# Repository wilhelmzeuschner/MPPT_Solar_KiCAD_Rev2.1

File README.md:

# Maximum Power Point Tracker for Solar Panels

This project was done as part of my studies at university. It's intended use case is for my [University's solar boat team](https://www.hs-emden-leer.de/studierende/fachbereiche/technik/projekte/solarboot).

## Technical Overview:

- 150W input power
- Boost Converter: Uin < Uout
- STM32 Microcontroller
- CAN Communications (software support lacking as of April 2022)

## How to use this repo:

### Schematic:
The schematic can be found here: https://github.com/wilhelmzeuschner/MPPT_Solar_KiCAD_Rev2.1/blob/main/pcb/export/Schematic.pdf

### Code:
The source code is located here: https://github.com/wilhelmzeuschner/MPPT_Solar_KiCAD_Rev2.1/tree/main/code/MPPT_Main

Platform IO was used for programming, just clone the repo and open the folder / workspace. The Arduino framework was used for the firmware.

### PCB:
The PCB was designed with KiCAD V6, the files are located here: https://github.com/wilhelmzeuschner/MPPT_Solar_KiCAD_Rev2.1/tree/main/pcb/kicad_files

### Bill of Materials (BOM):
The BOM file is also provided, although some parts are not available as of April 2022 due to the semiconductor shortage.
https://github.com/wilhelmzeuschner/MPPT_Solar_KiCAD_Rev2.1/tree/main/bom

### CAD Files for a 3D-printable Case:
https://github.com/wilhelmzeuschner/MPPT_Solar_KiCAD_Rev2.1/tree/main/cad

## Further documentation:

This project was documented extensively. The technical report can be found here:
https://github.com/wilhelmzeuschner/MPPT_Solar_KiCAD_Rev2.1/blob/main/doc/latex/pdf/Projektarbeit_MPPT_Wilhelm_Zeuschner_GitHub.pdf

### License:

MIT License

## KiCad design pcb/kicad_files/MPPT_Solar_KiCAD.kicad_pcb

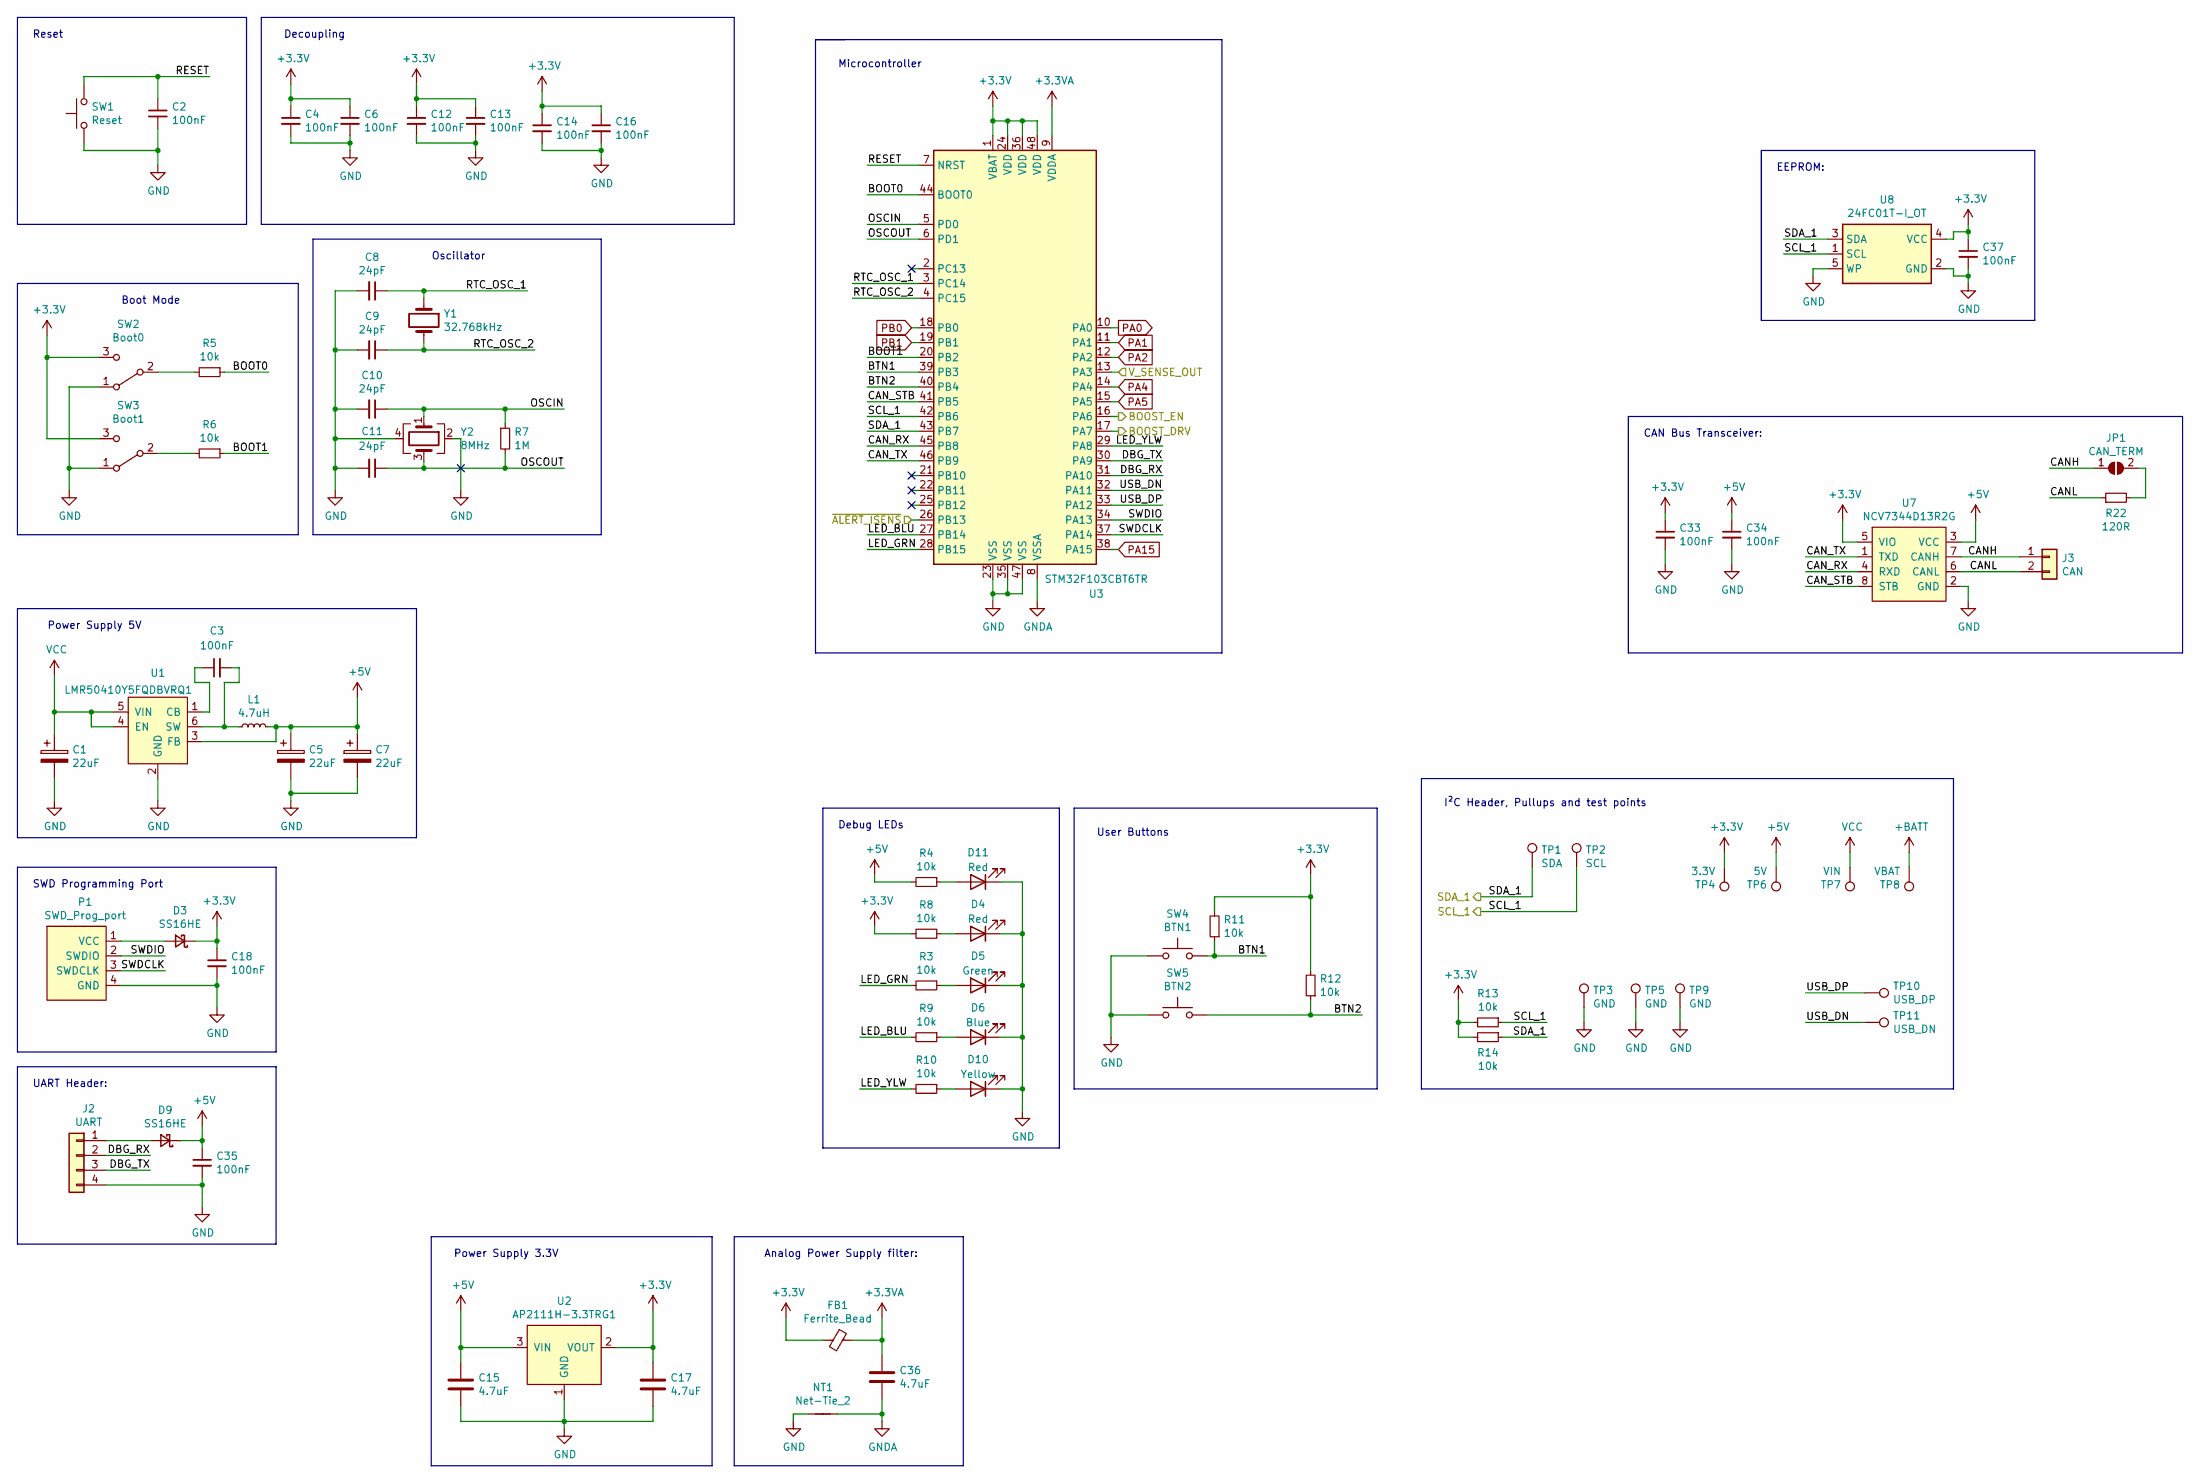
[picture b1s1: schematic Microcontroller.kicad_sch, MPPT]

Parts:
C1, C5, C7: 22uF; CP_Elec_5x5.9; Manufacturer Part Number 865080643008; Digikey Part No PCE5022CT-ND
C2, C3, C4, C6, C12, C13, C14, C16, C18, C33, C34, C35, C37: 100nF; C_0603_1608Metric; Manufacturer Part Number LMK063C6104KP-F; Digikey Part No 1276-CL10B104KB8NNNLCT-ND
C8, C9, C10, C11: 24pF; C_0603_1608Metric; Manufacturer Part Number 80-C0603C240G1HACTU; Digikey Part No 1276-1761-1-ND
C15, C17, C36: 4.7uF; C_0805_2012Metric; Manufacturer Part Number 885012107013; Digikey Part No 1276-1244-1-ND
D3, D9: SS16HE; D_SOD-323; Manufacturer Part Number SS16HE; Digikey Part No SS16HECT-ND
D4, D11: Red; LED_0805_2012Metric; Manufacturer Part Number 150080RS75000; Digikey Part No 732-4984-1-ND
D5: Green; LED_0805_2012Metric; Manufacturer Part Number 150080GS75000; Digikey Part No 732-4983-1-ND
D6: Blue; LED_0805_2012Metric; Manufacturer Part Number 150080BS75000; Digikey Part No 732-4982-1-ND
D10: Yellow; LED_0805_2012Metric; Manufacturer Part Number 150080YS75000; Digikey Part No 732-4987-1-ND
FB1: Ferrite_Bead; L_0603_1608Metric; Manufacturer Part Number BLM18TG102TN1D; Digikey Part No 490-9701-1-ND
J2: UART; PinHeader_1x04_P2.54mm_Vertical; Manufacturer Part Number RS1-04-G; Digikey Part No 2057-RS1-04-G-ND
J3: CAN; 1713017; Manufacturer Part Number 1713017; Digikey Part No 277-8591-ND
JP1: CAN_TERM; SolderJumper-2_P1.3mm_Open_RoundedPad1.0x1.5mm
L1: 4.7uH; 60x60mm_Inductor; Manufacturer Part Number NRS6028T4R7MMGK; Digikey Part No 587-2943-1-ND
NT1: Net-Tie_2; NetTie-2_SMD_Pad0.5mm
P1: SWD_Prog_port; PinSocket_1x04_P2.54mm_Vertical; Manufacturer Part Number RS1-04-G; Digikey Part No 2057-RS1-04-G-ND
R3, R4, R5, R6, R8, R9, R10, R11, R12, R13, R14: 10k; R_0603_1608Metric; Manufacturer Part Number RC0603FR-0710KL; Digikey Part No 311-10.0KHRCT-ND
R7: 1M; R_0603_1608Metric; Manufacturer Part Number RC0603FR-071ML; Digikey Part No 311-1.00MHRCT-ND
R22: 120R; R_1206_3216Metric; Manufacturer Part Number RC1206FR-07120RL; Digikey Part No 311-120FRCT-ND
SW1: Reset; SW_SPST_EVQPE1; Manufacturer Part Number CKN12317-1-ND; Digikey Part No CKN12317-1-ND
SW2: Boot0; SW_JS202011JCQN; Manufacturer Part Number JS202011JCQN; Digikey Part No CKN10723CT-ND
SW3: Boot1; SW_JS202011JCQN; Manufacturer Part Number JS202011JCQN; Digikey Part No CKN10723CT-ND
SW4: BTN1; SW_SPST_EVQPE1; Manufacturer Part Number CKN12317-1-ND; Digikey Part No CKN12317-1-ND
SW5: BTN2; SW_SPST_EVQPE1; Manufacturer Part Number CKN12317-1-ND; Digikey Part No CKN12317-1-ND
TP1: SDA; TestPoint_Pad_D1.0mm
TP2: SCL; TestPoint_Pad_D1.0mm
TP3, TP5, TP9: GND; TestPoint_Pad_D1.0mm
TP4: 3.3V; TestPoint_Pad_D1.0mm
TP6: 5V; TestPoint_Pad_D1.0mm
TP7: VIN; TestPoint_Pad_D1.0mm
TP8: VBAT; TestPoint_Pad_D1.0mm
TP10: USB_DP; TestPoint_Pad_D1.0mm
TP11: USB_DN; TestPoint_Pad_D1.0mm
U1: LMR50410Y5FQDBVRQ1; SOT-23-6; Manufacturer Part Number LMR50410Y5FQDBVRQ1; Digikey Part No 296-LMR50410Y5FQDBVRQ1CT-ND
U2: AP2111H-3.3TRG1; SOT-223-3_TabPin2; Manufacturer Part Number AP2111H-3.3TRG1; Digikey Part No AP2111H-3.3TRG1DICT-ND
U3: STM32F103CBT6TR; LQFP-48_7x7mm_P0.5mm; Manufacturer Part Number STM32F103CBT6TR; Digikey Part No 497-17380-1-ND
U7: NCV7344D13R2G; SOIC-8_3.9x4.9mm_P1.27mm; Manufacturer Part Number NCV7344D13R2G; Digikey Part No NCV7344D13R2GOSCT-ND
U8: 24FC01T-I_OT; SOT-23-5; Manufacturer Part Number 24FC01T-I/OT; Digikey Part No 24FC01T-I/OTCT-ND
Y1: 32.768kHz; Crystal_SMD_MicroCrystal_CC7V-T1A-2Pin_3.2x1.5mm; Manufacturer Part Number FC-135R 32.7680KF-A3; Digikey Part No SER4076CT-ND
Y2: 8MHz; Crystal_SMD_3225-4Pin_3.2x2.5mm; Manufacturer Part Number ECS-80-12-33Q-GN-TR; Digikey Part No 50-ECS-80-12-33Q-GN-CT-ND

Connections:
+3.3VA: C36.1, FB1.1, U3.9 (VDDA); also elsewhere on the board
+3V3: C4.1, C6.1, C12.1, C13.1, C14.1, C16.1, C17.1, C18.1, C33.1, C37.1, D3.1 (K), FB1.2, R8.2, R11.2, R12.2, R13.2, R14.2, SW2.3 (C), SW3.3 (C), TP4.1, U2.2 (VOUT), U2.4 (VOUT), U3.1 (VBAT), U3.24 (VDD), U3.36 (VDD), U3.48 (VDD), U7.5 (VIO), U8.4 (VCC); also elsewhere on the board
+5V: C5.1, C7.1, C15.1, C34.1, C35.1, D9.1 (K), L1.2, R4.2, TP6.1, U1.3 (FB), U2.3 (VIN), U7.3 (VCC)
+BATT: TP8.1; also elsewhere on the board
/MPPT_Boost_Converter/BOOST_DRV: U3.17 (PA7); also elsewhere on the board
/MPPT_Boost_Converter/BOOST_EN: U3.16 (PA6); also elsewhere on the board
/MPPT_Boost_Converter/V_SENSE_OUT: U3.13 (PA3); also elsewhere on the board
/MPPT_Boost_Converter/~ALERT_ISENS: U3.26 (PB13); also elsewhere on the board
/Microcontroller/BOOT0: R5.1, U3.44 (BOOT0)
/Microcontroller/BOOT1: R6.1, U3.20 (PB2)
/Microcontroller/BTN1: R11.1, SW4.2, U3.39 (PB3)
/Microcontroller/BTN2: R12.1, SW5.2, U3.40 (PB4)
/Microcontroller/CANH: J3.1, JP1.1 (A), U7.7 (CANH)
/Microcontroller/CANL: J3.2, R22.1, U7.6 (CANL)
/Microcontroller/CAN_RX: U3.45 (PB8), U7.4 (RXD)
/Microcontroller/CAN_STB: U3.41 (PB5), U7.8 (STB)
/Microcontroller/CAN_TX: U3.46 (PB9), U7.1 (TXD)
/Microcontroller/DBG_RX: J2.2, U3.31 (PA10)
/Microcontroller/DBG_TX: J2.3, U3.30 (PA9)
/Microcontroller/LED_BLU: R9.2, U3.27 (PB14)
/Microcontroller/LED_GRN: R3.2, U3.28 (PB15)
/Microcontroller/LED_YLW: R10.2, U3.29 (PA8)
/Microcontroller/OSCIN: C10.1, R7.1, U3.5 (PD0), Y2.1
/Microcontroller/OSCOUT: C11.1, R7.2, U3.6 (PD1), Y2.3
/Microcontroller/RESET: C2.1, SW1.2, U3.7 (NRST)
/Microcontroller/RTC_OSC_1: C8.1, U3.3 (PC14), Y1.1
/Microcontroller/RTC_OSC_2: C9.1, U3.4 (PC15), Y1.2
/Microcontroller/SCL_1: R13.1, TP2.1, U3.42 (PB6), U8.1 (SCL); also elsewhere on the board
/Microcontroller/SDA_1: R14.1, TP1.1, U3.43 (PB7), U8.3 (SDA); also elsewhere on the board
/Microcontroller/SWDCLK: P1.3 (SWDCLK), U3.37 (PA14)
/Microcontroller/SWDIO: P1.2 (SWDIO), U3.34 (PA13)
/Microcontroller/USB_DN: TP11.1, U3.32 (PA11)
/Microcontroller/USB_DP: TP10.1, U3.33 (PA12)
GND: C1.2, C2.2, C4.2, C5.2, C6.2, C7.2, C8.2, C9.2, C10.2, C11.2, C12.2, C13.2, C14.2, C15.2, C16.2, C17.2, C18.2, C33.2, C34.2, C35.2, C37.2, D4.1 (K), D5.1 (K), D6.1 (K), D10.1 (K), D11.1 (K), J2.4, NT1.1, P1.4 (GND), SW1.1, SW2.1 (A), SW3.1 (A), SW4.1, SW5.1, TP3.1, TP5.1, TP9.1, U1.2 (GND), U2.1 (GND), U3.23 (VSS), U3.35 (VSS), U3.47 (VSS), U7.2 (GND), U8.2 (GND), U8.5 (WP), Y2.2, Y2.4; also elsewhere on the board
GNDA: C36.2, NT1.2, U3.8 (VSSA); also elsewhere on the board
unnamed: C3.1, U1.1 (CB)
unnamed: C3.2, L1.1, U1.6 (SW)
unnamed: D3.2 (A), P1.1 (VCC)
unnamed: D4.2 (A), R8.1
unnamed: D5.2 (A), R3.1
unnamed: D6.2 (A), R9.1
unnamed: D9.2 (A), J2.1
unnamed: D10.2 (A), R10.1
unnamed: D11.2 (A), R4.1
unnamed: JP1.2 (B), R22.2
unnamed: R5.2, SW2.2 (B)
unnamed: R6.2, SW3.2 (B)
PA0: U3.10 (PA0)
PA1: U3.11 (PA1)
PA2: U3.12 (PA2)
PA4: U3.14 (PA4)
PA5: U3.15 (PA5)
PA15: U3.38 (PA15)
PB0: U3.18 (PB0)
PB1: U3.19 (PB1)
VCC: C1.1, TP7.1, U1.4 (EN), U1.5 (VIN); also elsewhere on the board

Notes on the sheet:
CAN Bus Transceiver:
EEPROM:
Power Supply 3.3V
Reset
User Buttons
Analog Power Supply filter:
Microcontroller
SWD Programming Port
Power Supply 5V
Boot Mode
Decoupling
UART Header:
Debug LEDs
I²C Header, Pullups and test points
Oscillator

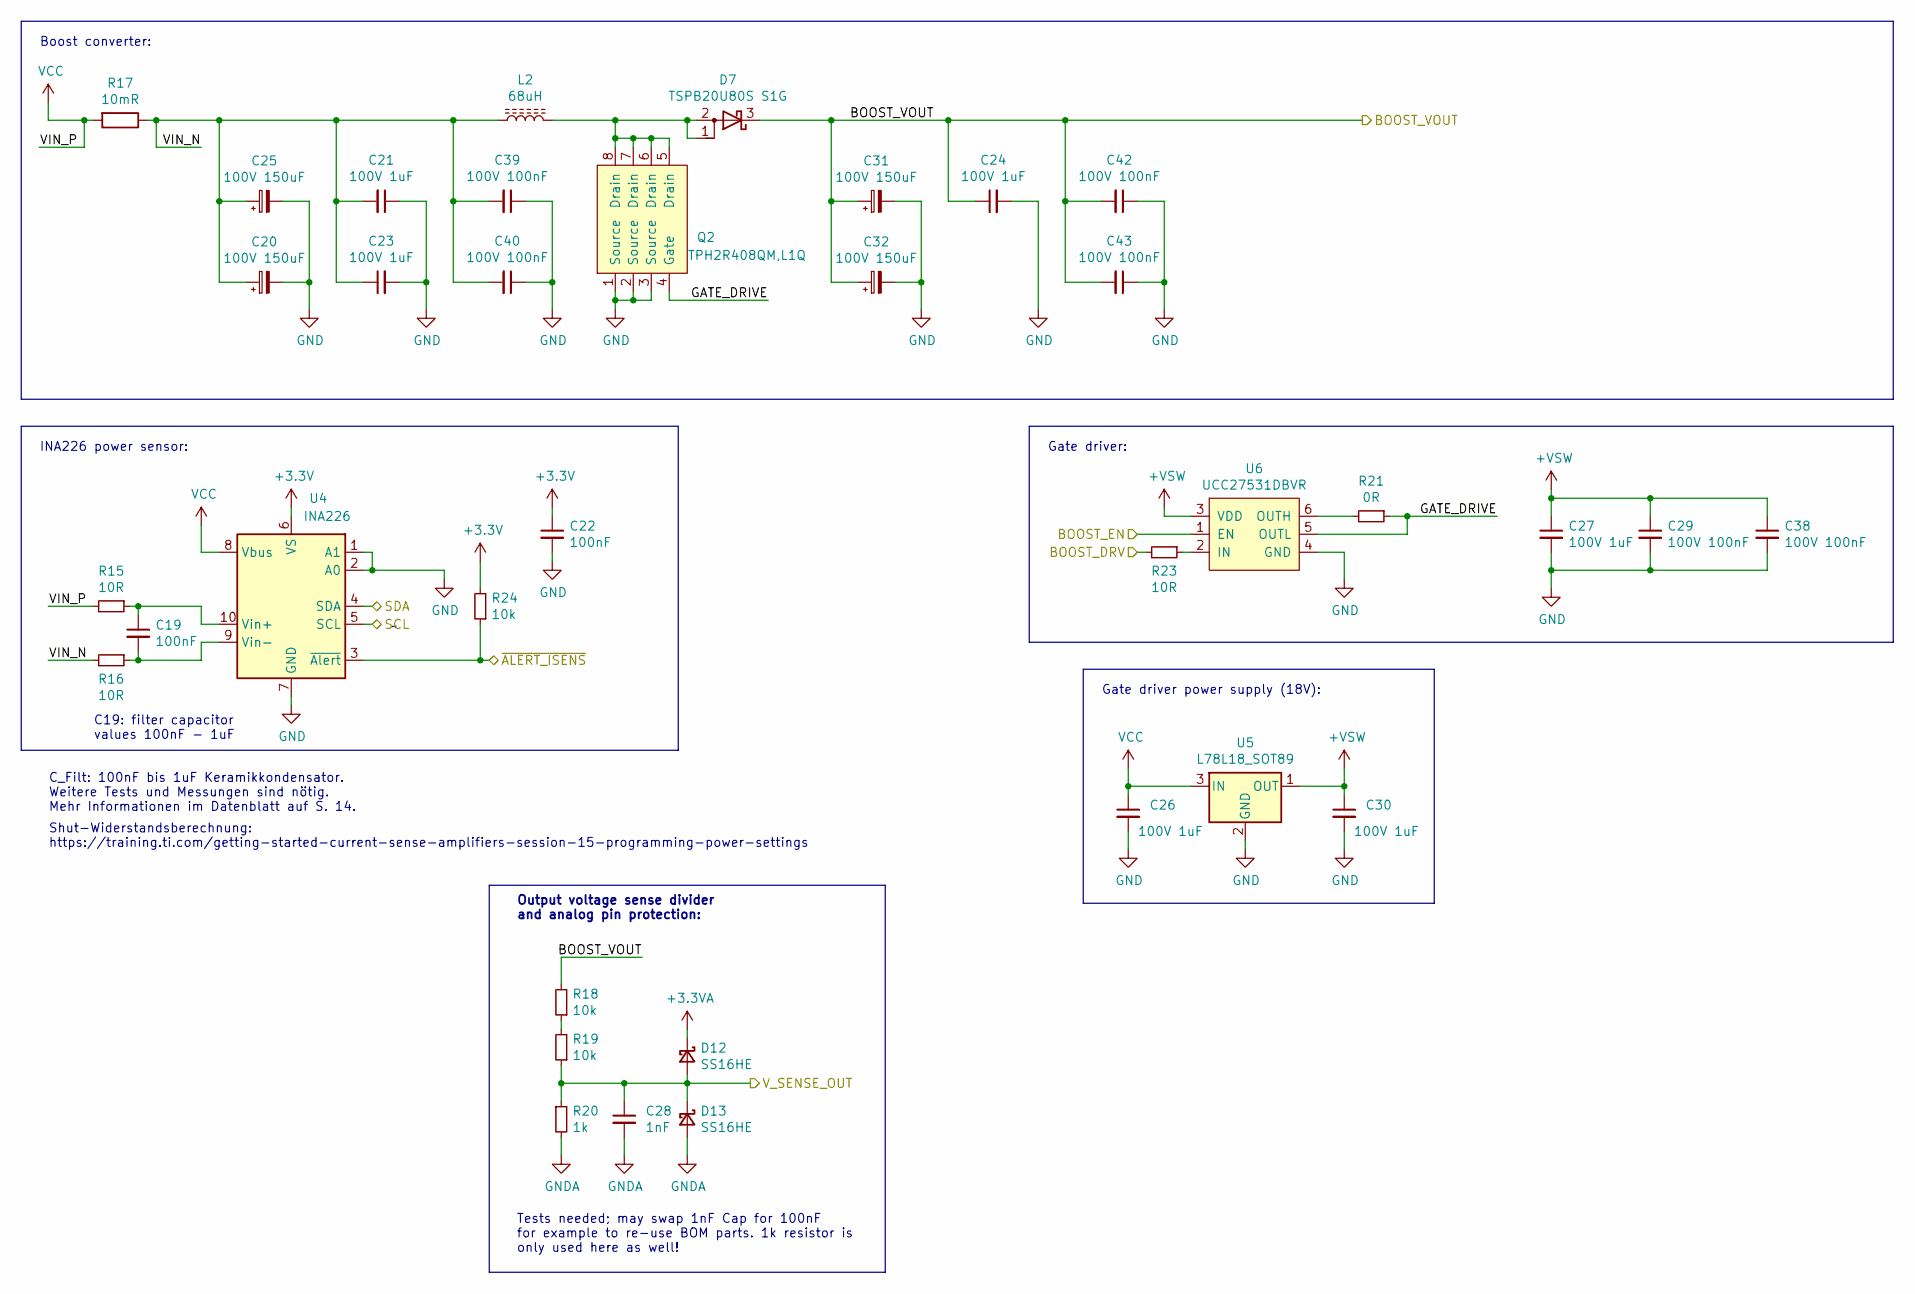
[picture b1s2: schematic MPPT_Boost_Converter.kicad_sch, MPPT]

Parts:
C19, C22: 100nF; C_0603_1608Metric; Manufacturer Part Number LMK063C6104KP-F; Digikey Part No 1276-CL10B104KB8NNNLCT-ND
C20, C25, C31, C32: 100V 150uF; CAPAE1300X1650N; Manufacturer Part Number EMHS101ARA151MKG5S; Digikey Part No 565-5086-1-ND
C21, C23, C24, C26, C27, C30: 100V 1uF; C_1206_3216Metric; Manufacturer Part Number HMK316BJ105KL-T; Digikey Part No 587-5021-1-ND
C28: 1nF; C_0603_1608Metric; Manufacturer Part Number C0603C102J5RACAUTO; Digikey Part No 399-12989-1-ND
C29, C38, C39, C40, C42, C43: 100V 100nF; C_0603_1608Metric; Manufacturer Part Number CL10B104KC8NNNC; Digikey Part No 587-6323-1-ND
D7: TSPB20U80S S1G; TO-277A; Manufacturer Part Number TSPB20U80S S1G; Digikey Part No TSPB20U80SS1GCT-ND
D12, D13: SS16HE; D_SOD-323; Manufacturer Part Number SS16HE; Digikey Part No SS16HECT-ND
L2: 68uH; 74437429203680; Manufacturer Part Number 74437429203680; Digikey Part No 732-11708-ND
Q2: TPH2R408QM,L1Q; SOP_ADVANCE; Manufacturer Part Number TPH2R408QM,L1Q; Digikey Part No 264-TPH2R408QML1QCT-ND
R15, R16, R23: 10R; R_0603_1608Metric; Manufacturer Part Number RMCF0603FT10R0; Digikey Part No RMCF0603FT10R0CT-ND
R17: 10mR; R_0612_1632Metric; Manufacturer Part Number CFG0612-FX-R010ELF; Digikey Part No CFG0612-FX-R010ELFCT-ND
R18, R19, R24: 10k; R_0603_1608Metric; Manufacturer Part Number RC0603FR-0710KL; Digikey Part No 311-10.0KHRCT-ND
R20: 1k; R_0603_1608Metric; Manufacturer Part Number CRCW06031K00FKEAC; Digikey Part No 541-3949-1-ND
R21: 0R; R_0603_1608Metric; Manufacturer Part Number RC0603FR-070RL; Digikey Part No 311-0.0HRCT-ND
U4: INA226; VSSOP-10_3x3mm_P0.5mm; Manufacturer Part Number INA226AIDGSR; Digikey Part No 296-29034-1-ND
U5: L78L18_SOT89; SOT-89-3; Manufacturer Part Number L78L18ACUTR; Digikey Part No 497-7280-1-ND
U6: UCC27531DBVR; SOT-23-6; Manufacturer Part Number UCC27531DBVR; Digikey Part No 296-35581-1-ND

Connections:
+3.3VA: D12.1 (K); also elsewhere on the board
+3V3: C22.1, R24.2, U4.6 (VS); also elsewhere on the board
+VSW: C27.1, C29.1, C30.1, C38.1, U5.1 (OUT), U6.3 (VDD)
/MPPT_Boost_Converter/BOOST_DRV: R23.2; also elsewhere on the board
/MPPT_Boost_Converter/BOOST_EN: U6.1 (EN); also elsewhere on the board
/MPPT_Boost_Converter/BOOST_VOUT: C24.1, C31.1, C32.1, C42.2, C43.2, D7.3 (K), R18.2; also elsewhere on the board
/MPPT_Boost_Converter/GATE_DRIVE: Q2.4 (Gate), R21.1, U6.5 (OUTL)
/MPPT_Boost_Converter/VIN_N: C20.1, C21.2, C23.1, C25.1, C39.2, C40.2, L2.1, R16.2, R17.1
/MPPT_Boost_Converter/V_SENSE_OUT: C28.1, D12.2 (A), D13.1 (K), R19.1, R20.1; also elsewhere on the board
/MPPT_Boost_Converter/~ALERT_ISENS: R24.1, U4.3 (~Alert); also elsewhere on the board
/Microcontroller/SCL_1: U4.5 (SCL); also elsewhere on the board
/Microcontroller/SDA_1: U4.4 (SDA); also elsewhere on the board
GND: C20.2, C21.1, C22.2, C23.2, C24.2, C25.2, C26.2, C27.2, C29.2, C30.2, C31.2, C32.2, C38.2, C39.1, C40.1, C42.1, C43.1, Q2.1 (Source), Q2.2 (Source), Q2.3 (Source), U4.1 (A1), U4.2 (A0), U4.7 (GND), U5.2 (GND), U6.4 (GND); also elsewhere on the board
GNDA: C28.2, D13.2 (A), R20.2; also elsewhere on the board
unnamed: C19.1, R15.1, U4.10 (Vin+)
unnamed: C19.2, R16.1, U4.9 (Vin-)
unnamed: D7.1 (A), D7.2 (A), L2.2, Q2.5 (Drain), Q2.6 (Drain), Q2.7 (Drain), Q2.8 (Drain)
unnamed: R18.1, R19.2
unnamed: R21.2, U6.6 (OUTH)
unnamed: R23.1, U6.2 (IN)
VCC: C26.1, R15.2, R17.2, U4.8 (Vbus), U5.3 (IN); also elsewhere on the board

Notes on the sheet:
Output voltage sense divider and analog pin protection:
C19: filter capacitor values 100nF - 1uF
Boost converter:
Shut-Widerstandsberechnung: https://training.ti.com/getting-started-current-sense-amplifiers-session-15-programming-power-settings
Gate driver:
Gate driver power supply (18V):
Tests needed; may swap 1nF Cap for 100nF for example to re-use BOM parts. 1k resistor is only used here as well!
INA226 power sensor:
C_Filt: 100nF bis 1uF Keramikkondensator. Weitere Tests und Messungen sind nötig. Mehr Informationen im Datenblatt auf S. 14.

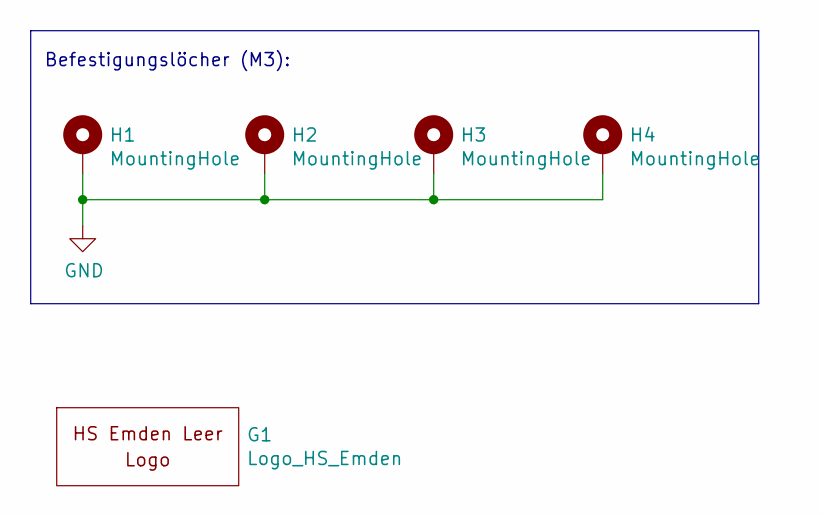
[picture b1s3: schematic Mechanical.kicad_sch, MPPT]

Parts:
G1: Logo_HS_Emden; HS_Logo
H1, H2, H3, H4: MountingHole; MountingHole_3.2mm_M3_Pad_Via

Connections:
GND: H1.1, H2.1, H3.1, H4.1; also elsewhere on the board

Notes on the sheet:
Befestigungslöcher (M3):

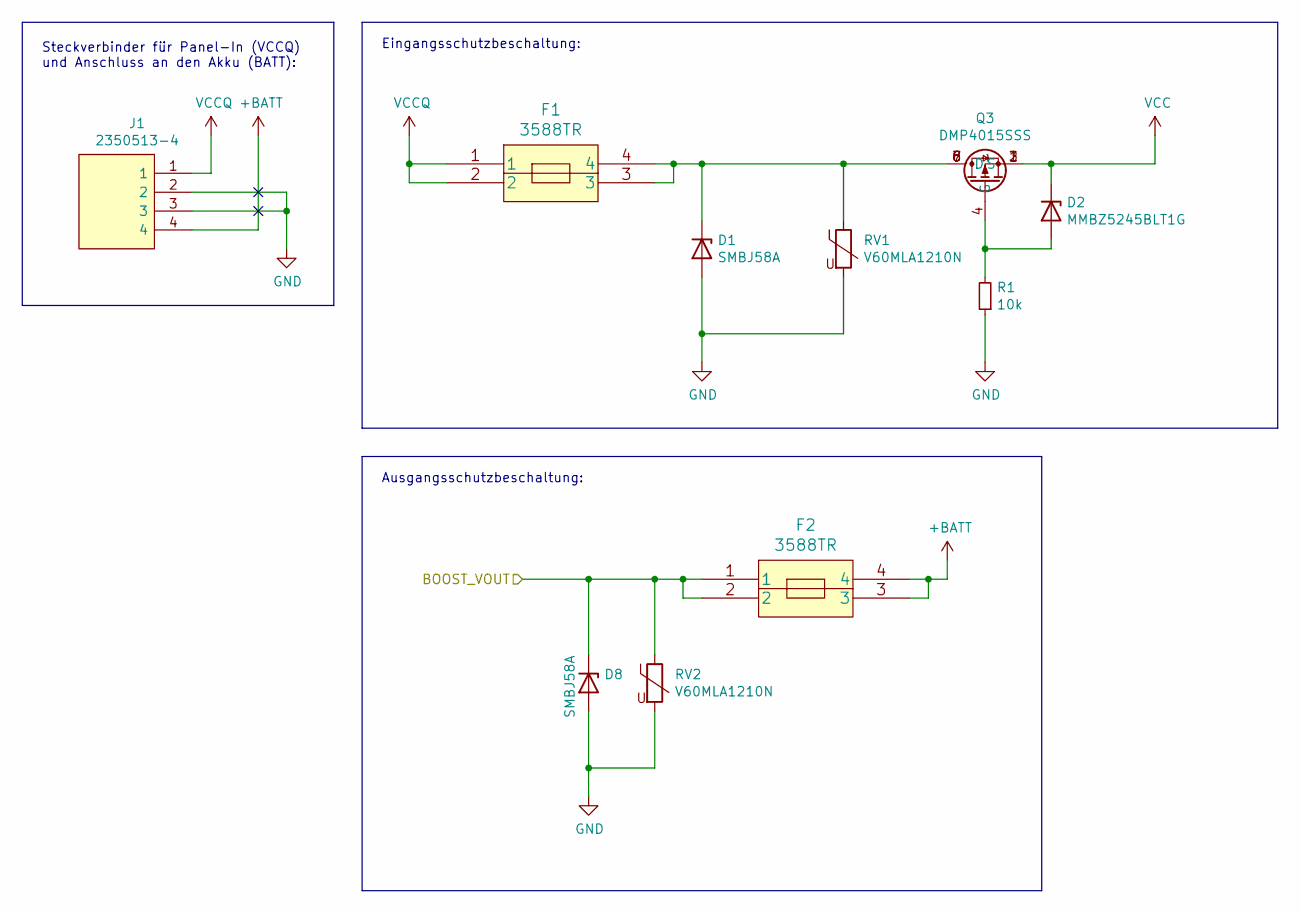
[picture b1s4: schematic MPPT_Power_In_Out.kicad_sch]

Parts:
D1, D8: SMBJ58A; D_SMB; Manufacturer Part Number SMBJ58A; Digikey Part No SMBJ58ALFCT-ND
D2: MMBZ5245BLT1G; D_SOT-23_ANK; Manufacturer Part Number MMBZ5245BLT1G; Digikey Part No MMBZ5245BLT1GOSCT-ND
F1, F2: 3588TR; Manufacturer Part Number 3588TR; Digikey Part No 36-3588CT-ND
J1: 2350513-4; SHDRRA4W110P0X500_1X4_2160X830X1230P; Manufacturer Part Number 2350513-4; Digikey Part No A145374-ND
Q3: DMP4015SSS; SO-8_3.9x4.9mm_P1.27mm; Manufacturer Part No DMP4015SSS-13; Digi-Key Part No DMP4015SSS-13DICT-ND
R1: 10k; R_0603_1608Metric; Manufacturer Part Number RC0603FR-0710KL; Digikey Part No 311-10.0KHRCT-ND
RV1, RV2: V60MLA1210N; R_1210_3225Metric; Manufacturer Part Number V60MLA1210NH; Digikey Part No F3830CT-ND

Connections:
+BATT: F2.3, F2.4, J1.4; also elsewhere on the board
/MPPT_Boost_Converter/BOOST_VOUT: D8.1 (K), F2.1, F2.2, RV2.1; also elsewhere on the board
GND: D1.2 (A), D8.2 (A), J1.2, J1.3, R1.1, RV1.2, RV2.2; also elsewhere on the board
unnamed: D1.1 (K), F1.3, F1.4, Q3.5 (D), Q3.6 (D), Q3.7 (D), Q3.8 (D), RV1.1
unnamed: D2.2 (A), Q3.4 (G), R1.2
VCC: D2.1 (K), Q3.1 (S), Q3.2 (S), Q3.3 (S); also elsewhere on the board
VCCQ: F1.1, F1.2, J1.1

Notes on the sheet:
Eingangsschutzbeschaltung:
Steckverbinder für Panel-In (VCCQ) und Anschluss an den Akku (BATT):
Ausgangsschutzbeschaltung:

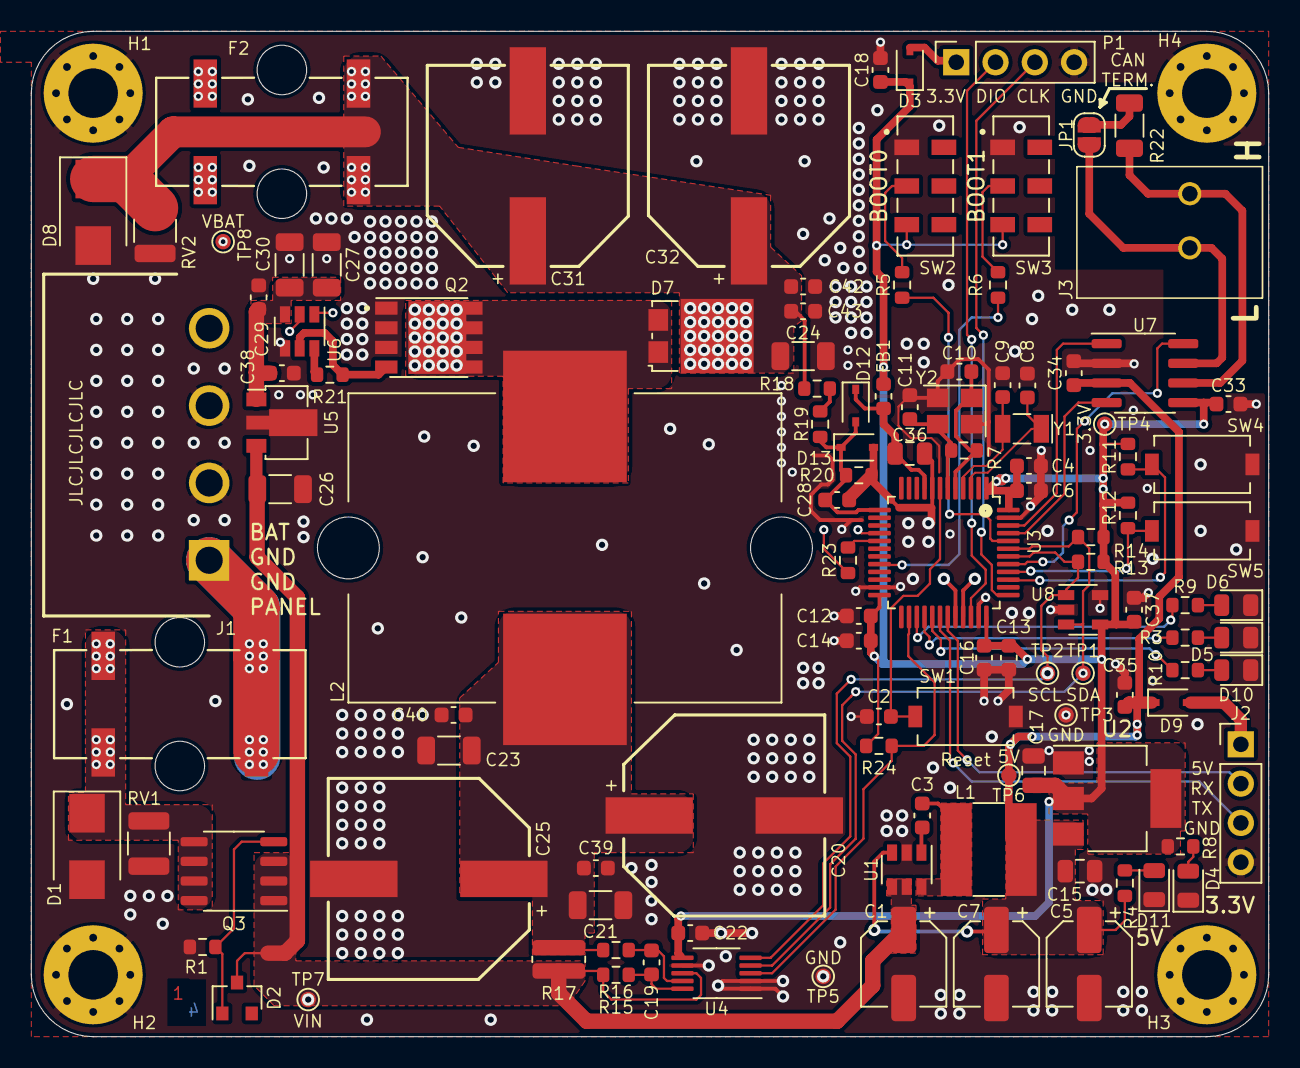
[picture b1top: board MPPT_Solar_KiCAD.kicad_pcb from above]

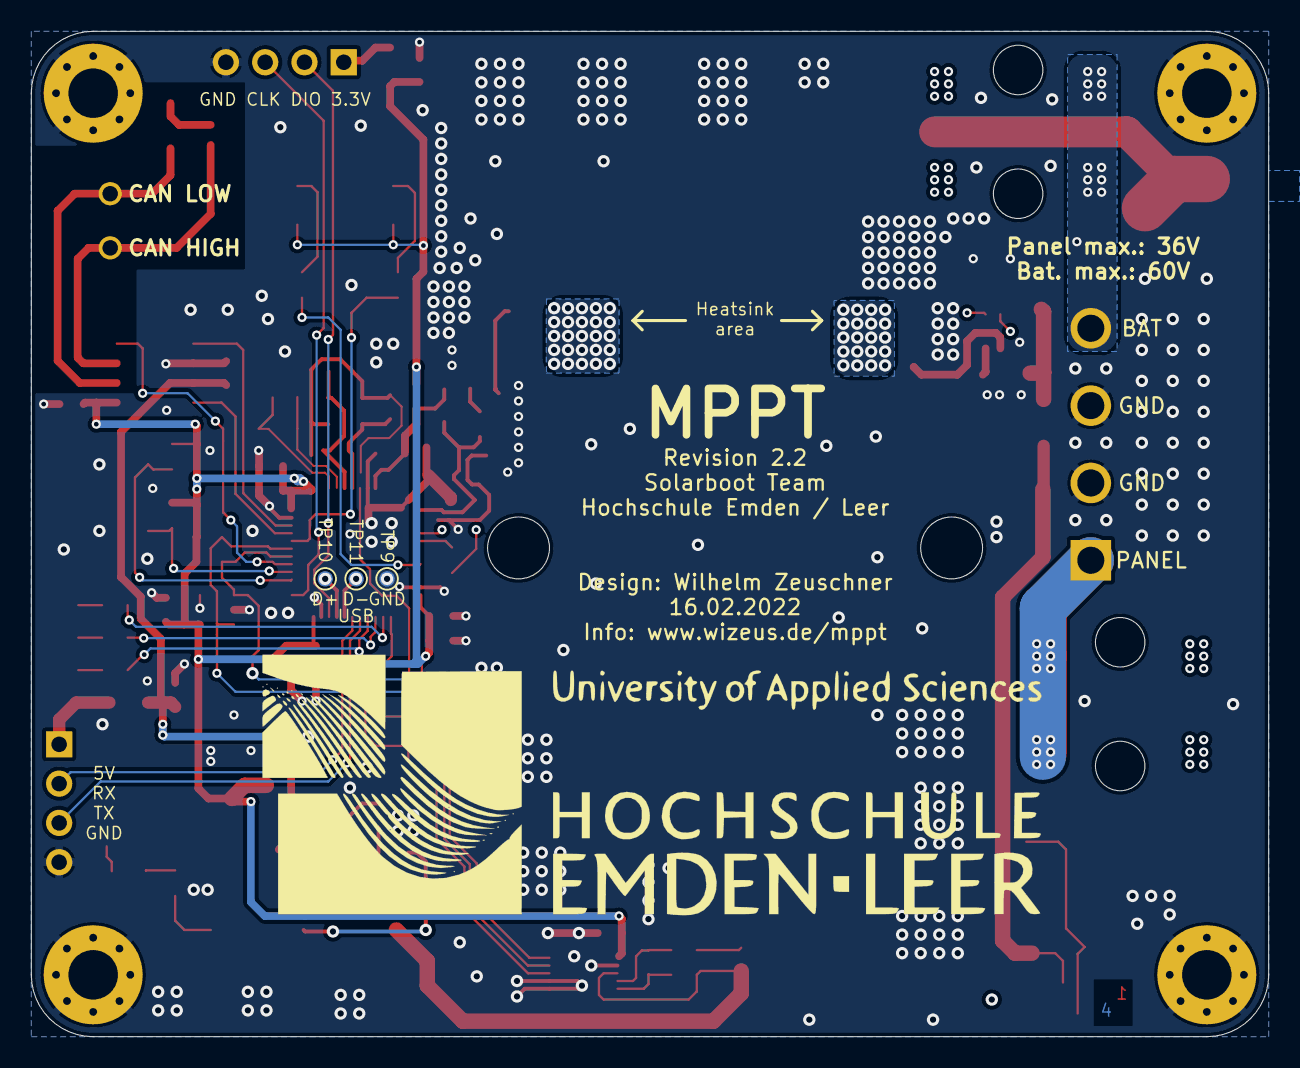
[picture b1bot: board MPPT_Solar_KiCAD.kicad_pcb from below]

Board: 4 copper layers, 80.0 x 65.0 mm, 124 parts (4 on the bottom side), 61 nets.

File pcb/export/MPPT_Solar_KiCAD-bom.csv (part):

Row,Description,Part,References,Value,Footprint,Quantity Per PCB,Status,Datasheet,Digikey Part No,Manufacturer Part Number,Mouser Part Number,Do not fit,Config,PDF,Note,MPN,Height,Manufacturer_Name,Manufacturer_Part_Number,Arrow Part Number,Mouser Price/Stock,Manufacturer Part No,Digi-Key Part No
1,"Unpolarized capacitor, small symbol",C_Small,C8 C9 C10 C11,24pF,C_0603_1608Metric,4, ,https://www.digikey.ch/product-detail/en/samsung-electro-mec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,1276-1761-1-ND,80-C0603C240G1HACTU,,,,,,,,,,,,,
2,"Unpolarized capacitor, small symbol",C_Small,C28,1nF,C_0603_1608Metric,1, ,https://www.digikey.ch/product-detail/en/kemet/C0603C102J5RA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,399-12989-1-ND,C0603C102J5RACAUTO,,,,,,,,,,,,,
3,"Unpolarized capacitor, small symbol",C_Small,C2 C3 C4 C6 C12 C13 C14 C16 C18 C19 C22 C33 C34 C35 C37,100nF,C_0603_1608Metric,15, ,https://www.digikey.ch/product-detail/en/samsung-electro-mec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,1276-CL10B104KB8NNNLCT-ND,LMK063C6104KP-F,,,,,,,,,,,,,
4,Unpolarized capacitor,C,C15 C17 C36,4.7uF,C_0805_2012Metric,3, ,https://www.digikey.ch/product-detail/en/samsung-electro-mec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,1276-1244-1-ND,885012107013,,,,,,,,,,,,,
5,Polarized capacitor,CP,C1 C5 C7,22uF,CP_Elec_5x5.9,3, ,https://www.digikey.de/product-detail/en/panasonic-electroni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,PCE5022CT-ND,865080643008,,,,,,,,,,,,,
6,"Unpolarized capacitor, small symbol",C_Small,C29 C38 C39 C40 C42 C43,100V 100nF,C_0603_1608Metric,6, ,https://www.digikey.ch/product-detail/en/taiyo-yuden/HMK107B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,587-6323-1-ND,CL10B104KC8NNNC,,,,,,,,,,,,,
7,"Polarized capacitor, small symbol",CP_Small,C20 C25 C31 C32,100V 150uF,CAPAE1300X1650N,4, ,https://www.digikey.de/product-detail/en/united-chemi-con/EM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,565-5086-1-ND,EMHS101ARA151MKG5S,,,,,,,,,,,,,
8,"Unpolarized capacitor, small symbol",C_Small,C21 C23 C24 C26 C27 C30,100V 1uF,C_1206_3216Metric,6, ,https://www.digikey.ch/product-detail/en/taiyo-yuden/HMK316B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,587-5021-1-ND,HMK316BJ105KL-T,,,,,,,,,,,,,
9,Light emitting diode,LED,D6,Blue,LED_0805_2012Metric,1, ,https://www.digikey.de/product-detail/en/würth-elektronik/15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,732-4982-1-ND,150080BS75000,,,,,,,,,,,,,
10,Light emitting diode,LED,D5,Green,LED_0805_2012Metric,1, ,https://www.digikey.de/product-detail/en/würth-elektronik/15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,732-4983-1-ND,150080GS75000,,,,,,,,,,,,,
11,Zener diode,D_Zener,D2 D14,MMBZ5245BLT1G,D_SOT-23_ANK,2, ,https://www.digikey.de/product-detail/en/on-semiconductor/MM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,MMBZ5245BLT1GOSCT-ND,MMBZ5245BLT1G,,,,,,,,,,,,,
12,Light emitting diode,LED,D4 D11,Red,LED_0805_2012Metric,2, ,https://www.digikey.de/product-detail/en/würth-elektronik/15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,732-4984-1-ND,150080RS75000,,,,,,,,,,,,,
13,Zener diode,D_Zener,D1 D8,SMBJ58A,D_SMB,2, ,https://www.digikey.de/product-detail/en/littelfuse-inc/SMBJ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,SMBJ58ALFCT-ND,SMBJ58A,,,,,,,,,,,,,
14,"Schottky diode, small symbol",D_Schottky_Small,D3 D9 D12 D13,SS16HE,D_SOD-323,4, ,https://www.digikey.de/product-detail/en/on-semiconductor/SS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,SS16HECT-ND,SS16HE,,,,,,,,,,,,,
15,"Schottky diode, anode on pins 1 and 2",V15P8HM3_A_H,D7,TSPB20U80S S1G,TO-277A,1, ,https://www.digikey.de/product-detail/en/taiwan-semiconducto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,TSPB20U80SS1GCT-ND,TSPB20U80S S1G,,,,,,,,,,,,,
16,Light emitting diode,LED,D10,Yellow,LED_0805_2012Metric,1, ,https://www.digikey.de/product-detail/en/würth-elektronik/15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,732-4987-1-ND,150080YS75000,,,,,,,,,,,,,
17,,3588TR,F1 F2,3588TR,3588TR,2, ,https://www.digikey.de/product-detail/en/keystone-electronic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,36-3588CT-ND,3588TR,,,,,Fuse: 0297010.WXNV https://www.digikey.de/product-detail/en/littelfuse-inc/0297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,,,,,,,,
18,"Ferrite bead, small symbol",Ferrite_Bead_Small,FB1,Ferrite_Bead,L_0603_1608Metric,1, ,https://www.digikey.de/product-detail/en/murata-electronics/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,490-9701-1-ND,BLM18TG102TN1D,,,,,,,,,,,,,
19,Pluggable Terminal Blocks 4pos Header 90 Deg 5.0mmTail Lgth 4.5mm,2350513-4,J1,2350513-4,SHDRRA4W110P0X500_1X4_2160X830X1230P,1, ,https://www.digikey.de/product-detail/en/te-connectivity-amp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,A145374-ND,2350513-4,,,,,Counterpart: A145365-ND (2350397-4),,,,,,,,
20,"Generic connector, single row, 01x02, script generated (kicad-library-utils/schlib/autogen/connector/)",Conn_01x02,J3,CAN,1713017,1, ,https://www.digikey.de/product-detail/en/phoenix-contact/171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,277-8591-ND,1713017,,,,,,,,,,,,,
21,"Generic connector, single row, 01x04, script generated (kicad-library-utils/schlib/autogen/connector/)",Conn_01x04,J2,UART,PinHeader_1x04_P2.54mm_Vertical,1, ,https://www.digikey.de/product-detail/en/adam-tech/RS1-04-G/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,2057-RS1-04-G-ND,RS1-04-G,,,,,,,,,,,,,
22,"Inductor, small symbol",L_Small,L1,4.7uH,60x60mm_Inductor,1, ,https://www.digikey.de/product-detail/en/taiyo-yuden/NRS6028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,587-2943-1-ND,NRS6028T4R7MMGK,,,,,,,,,,,,,
23,74437429203680 Inductor with ferrite core,68uH,L2,68uH,74437429203680,1, ,https://www.digikey.de/products/en?keywords=74437429203680,732-11708-ND,74437429203680,,,,,,,,,,,,,
24,,SWD_Prog_port,P1,SWD_Prog_port,PinSocket_1x04_P2.54mm_Vertical,1, ,https://www.digikey.de/product-detail/en/adam-tech/RS1-04-G/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,2057-RS1-04-G-ND,RS1-04-G,,,,,,,,,,,,,
25,PMOS,DMP4015SSS,Q3,DMP4015SSS,SO-8_3.9x4.9mm_P1.27mm,1, ,https://www.digikey.de/product-detail/en/diodes-incorporated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,,,,,,,,,,,,,,DMP4015SSS-13,DMP4015SSS-13DICT-ND
26,"Dual PMOS transistor, 8 pin package",Q_DUAL_PMOS_S1G1S2G2D2D2D1D1,Q1,DMP6050,SO-8_3.9x4.9mm_P1.27mm,1, ,~,,,,,,,,,,,,,,,
27,,TPH2R608NH,Q2,"TPH2R408QM,L1Q",SOP_ADVANCE,1, ,https://www.digikey.de/product-detail/en/toshiba-semiconduct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,264-TPH2R408QML1QCT-ND,"TPH2R408QM,L1Q",,,,,,,,,,,,,
28,"Resistor, small symbol",R_Small,R21,0R,R_0603_1608Metric,1, ,https://www.digikey.de/product-detail/en/yageo/RC0603FR-070R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,311-0.0HRCT-ND,RC0603FR-070RL,,,,,,,,,,,,,
29,Resistor,R,R17,10mR,R_0612_1632Metric,1, ,https://www.digikey.de/product-detail/en/bourns-inc/CFG0612-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,CFG0612-FX-R010ELFCT-ND,CFG0612-FX-R010ELF,,,,,,,,,,,,,
30,"Resistor, small symbol",R_Small,R15 R16 R23,10R,R_0603_1608Metric,3, ,https://www.digikey.de/product-detail/en/stackpole-electroni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,RMCF0603FT10R0CT-ND,RMCF0603FT10R0,,,,,,,,,,,,,
31,"Resistor, small symbol",R_Small,R22,120R,R_1206_3216Metric,1, ,https://www.digikey.de/product-detail/en/yageo/RC1206FR-0712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,311-120FRCT-ND,RC1206FR-07120RL,,,,,,,,,,,,,
32,"Resistor, small symbol",R_Small,R20,1k,R_0603_1608Metric,1, ,https://www.mouser.de/ProductDetail/Vishay-Dale/CRCW06031K00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,541-3949-1-ND,CRCW06031K00FKEAC,,,,,,,,,,,,,
33,"Resistor, small symbol",R_Small,R1 R2 R3 R4 R5 R6 R8 R9 R10 R11 R12 R13 R14 R18 R19 R24,10k,R_0603_1608Metric,16, ,https://www.mouser.de/ProductDetail/Yageo/RC0603FR-0710KL?qs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,311-10.0KHRCT-ND,RC0603FR-0710KL,,,,,,,,,,,,,
34,"Resistor, small symbol",R_Small,R7,1M,R_0603_1608Metric,1, ,https://www.mouser.de/ProductDetail/Yageo/RC0603FR-071ML?qs=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,311-1.00MHRCT-ND,RC0603FR-071ML,,,,,,,,,,,,,
35,Voltage dependent resistor,Varistor,RV1 RV2,V60MLA1210N,R_1210_3225Metric,2, ,https://www.digikey.de/product-detail/en/littelfuse-inc/V60M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,F3830CT-ND,V60MLA1210NH,,,,,,,,,,,,,
36,"Push button switch, generic, two pins",SW_Push,SW4,BTN1,SW_SPST_EVQPE1,1, ,https://www.digikey.de/product-detail/en/c-k/PTS636-SM43J-SM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,CKN12317-1-ND,CKN12317-1-ND,,,,,,,,,,,,,
37,"Push button switch, generic, two pins",SW_Push,SW5,BTN2,SW_SPST_EVQPE1,1, ,https://www.digikey.de/product-detail/en/c-k/PTS636-SM43J-SM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,CKN12317-1-ND,CKN12317-1-ND,,,,,,,,,,,,,
38,"Switch, single pole double throw",SW_SPDT,SW2,Boot0,SW_JS202011JCQN,1, ,https://www.digikey.de/product-detail/en/c-k/JS202011JCQN/CK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,CKN10723CT-ND,JS202011JCQN,,,,,,,,,,,,,
39,"Switch, single pole double throw",SW_SPDT,SW3,Boot1,SW_JS202011JCQN,1, ,https://www.digikey.de/product-detail/en/c-k/JS202011JCQN/CK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,CKN10723CT-ND,JS202011JCQN,,,,,,,,,,,,,
40,"Push button switch, generic, two pins",SW_Push,SW1,Reset,SW_SPST_EVQPE1,1, ,https://www.digikey.de/product-detail/en/c-k/PTS636-SM43J-SM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,CKN12317-1-ND,CKN12317-1-ND,,,,,,,,,,,,,
41,1KB I2C EEPROM 1MHZ 1.7-5.5V 5-S,24FC01T-I_OT,U8,24FC01T-I_OT,SOT-23-5,1, ,https://www.digikey.de/product-detail/en/microchip-technolog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,24FC01T-I/OTCT-ND,24FC01T-I/OT,,,,,,,,,,,,,
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
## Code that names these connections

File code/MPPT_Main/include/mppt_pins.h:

/*
Pin definitions
*/

#ifndef __MPPT_PINS
#define __MPPT_PINS


//LEDs for status indication etc.
#define LED1_PIN        PB_14        //Blue LED
#define LED2_PIN        PB_15        //Green LED
#define LED3_PIN        PA_8         //Red LED
#define LED_BLUE_PIN    LED1_PIN
#define LED_GREEN_PIN   LED2_PIN
#define LED_RED_PIN     LED3_PIN

//Buttons
#define BTN1_PIN        PB_3         //Top (SW4)
#define BTN2_PIN        PB_4         //Bottom (SW5)

//CAN Bus Pins
#define CAN_RX_PIN      PB_8
#define CAN_TX_PIN      PB_9
#define CAN_STBY_PIN    PB_5
#define CAN_STBY_ON     1
#define CAN_STBY_OFF    0

//Boost control pins
#define BOOST_DRIVE_PIN PA_7
#define BOOST_EN_PIN    PA_6
#define BOOST_EN_ON     1
#define BOOST_EN_OFF    0

//Output voltage sensing
#define V_SENSE_OUT_PIN PA_3

//INA226 signals
#define ALERT_ISENS_PIN PB_13        //Overcurrent alert input to STM32
#define SDA_1           PB_7
#define SCL_1           PB_6


#endif
